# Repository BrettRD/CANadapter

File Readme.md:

# CANadapter

This is a basic CAN bus adapter based on the MCP2515 and the MCP2551.
The design is largely compatible with the Sparkfun CAN-BUS Shield for the sake of everyone's sanity.

The connectors are intended to be pin-compatible with Pmod, but there doesn't seen to be a standard or even defacto pinout for CANbus on Pmod online.

Board images generated by gerblook.org

##Major design goals:
* Full electrical isolation
* Hardy CAN front-end
* Support CAN bus development on the FPGA driven icoBoard.

## Parts List:
### CAN interface:
* 1x MCP2551 soic8 - CAN interface chip
* 1x PESD1CAN sot23 - TVS diode
* 2x TLP2361 fast optocoupler - optoisolation
* 2x 60R 1210 resistor - termination resistors
* 1x 4.7nF 1206 capacitor - Common mode filter
* 1x 1uF 1206 capacitor
* 1x 100R 0603 resistor
* 1x 330R 0603 resistor
* 1x 4K7 0603 resistor
* 1x 4pin header

### CAN Controller:
* 1x MCP2515 soic18 7.5mm - CAN controller IC
* 1x 16MHz 5032 crystal
* 1x 1uF 1206 capacitor
* 2x 18pF 0603 capacitor
* 1x 2x6pin header

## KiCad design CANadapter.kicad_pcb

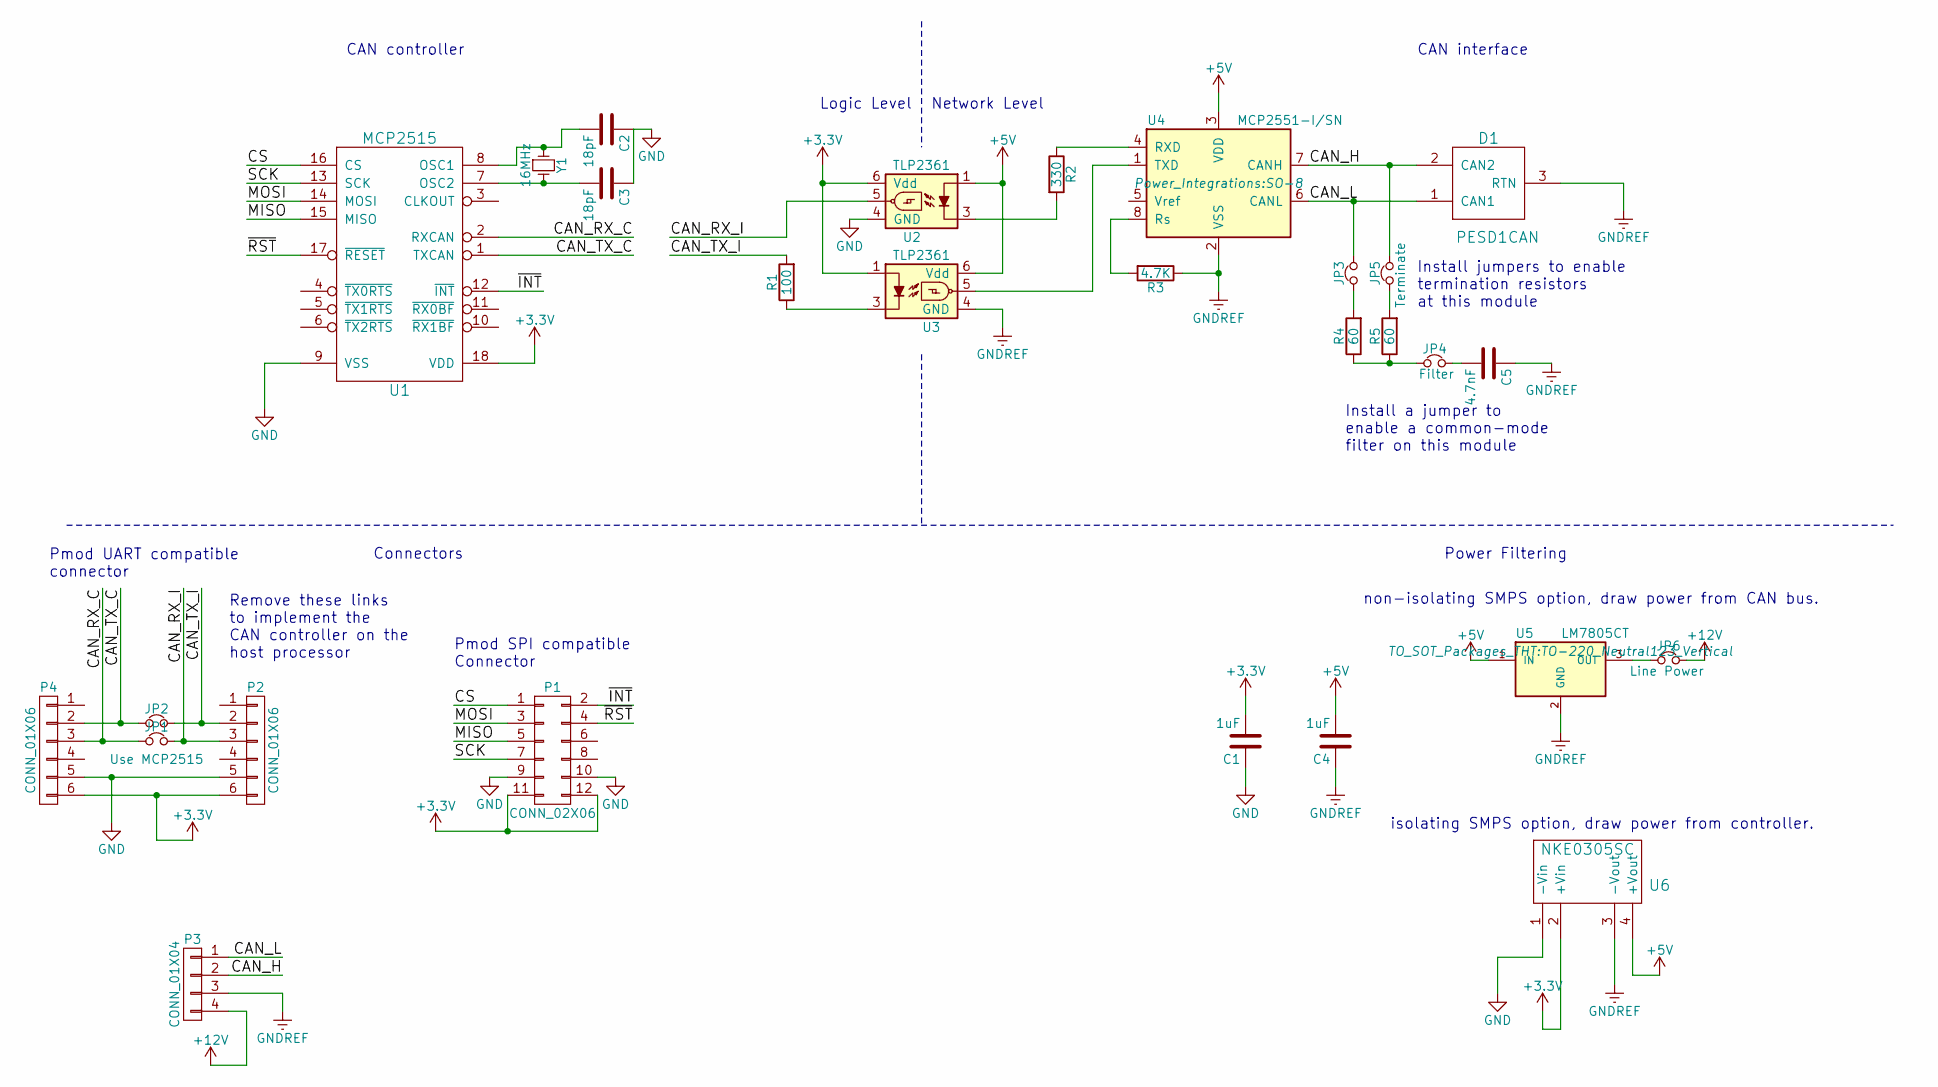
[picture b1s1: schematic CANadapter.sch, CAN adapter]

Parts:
C1, C4: 1uF; C_1210
C2, C3: 18pF; C_0603
C5: 4.7nF; C_1206
D1: PESD1CAN; SOT-23_Handsoldering
JP1, JP2: Use MCP2515; JumperSingleClosed
JP3, JP5: Terminate; JumperSingle
JP4: Filter; JumperSingle
JP6: Line Power; JumperSingle
P1: CONN_02X06; Pin_Header_Straight_2x06
P2, P4: CONN_01X06; Pin_Header_Straight_1x06
P3: CONN_01X04; Pin_Header_Straight_1x04
R1: 100; R_0603
R2: 330; R_0603
R3: 4.7K; R_0603
R4, R5: 60; R_1210
U1: MCP2515; SOIC-18_7.5x11.6mm_Pitch1.27mm
U2, U3: TLP2361; soic-5
U4: MCP2551-I/SN; SO-8
U5: LM7805CT; TO-220_Neutral123_Vertical
U6: NKE0305SC; Murata_SIL
Y1: 16MHz; Crystal_SMD_5032_2Pads

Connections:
+3V3: C1.2, P1.11, P1.12, P2.6, P4.6, U1.18 (VDD), U2.6 (Vdd), U3.1, U6.2 (+Vin)
+5V: C4.2, U2.1, U3.6 (Vdd), U4.3 (VDD), U5.1 (IN), U6.4 (+Vout)
+12V: JP6.1, P3.4
/CAN_H: D1.2 (CAN2), JP5.1, P3.2, U4.7 (CANH)
/CAN_L: D1.1 (CAN1), JP3.2, P3.1, U4.6 (CANL)
/CAN_RX_C: JP1.1, P4.3, U1.2 (RXCAN)
/CAN_RX_I: JP1.2, P2.3, U2.5
/CAN_TX_C: JP2.1, P4.2, U1.1 (TXCAN)
/CAN_TX_I: JP2.2, P2.2, R1.2
/CS: P1.1, U1.16 (CS)
/MISO: P1.5, U1.15 (MISO)
/MOSI: P1.3, U1.14 (MOSI)
/SCK: P1.7, U1.13 (SCK)
/~INT: P1.2, U1.12 (~INT)
/~RST: P1.4, U1.17 (~RESET)
GND: C1.1, C2.1, C3.1, P1.9, P1.10, P2.5, P4.5, U1.9 (VSS), U2.4 (GND), U6.1 (-Vin)
GNDREF: C4.1, C5.1, D1.3 (RTN), P3.3, R3.1, U3.4 (GND), U4.2 (VSS), U5.2 (GND), U6.3 (-Vout)
unnamed: C2.2, U1.8 (OSC1), Y1.1
unnamed: C3.2, U1.7 (OSC2), Y1.2
unnamed: C5.2, JP4.2
unnamed: JP3.1, R4.2
unnamed: JP4.1, R4.1, R5.1
unnamed: JP5.2, R5.2
unnamed: JP6.2, U5.3 (OUT)
unnamed: R1.1, U3.3
unnamed: R2.1, U4.4 (RXD)
unnamed: R2.2, U2.3
unnamed: R3.2, U4.8 (Rs)
unnamed: U3.5, U4.1 (TXD)

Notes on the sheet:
Pmod UART compatible connector
Logic Level
Network Level
Install jumpers to enable termination resistors at this module
Install a jumper to enable a common-mode filter on this module
Remove these links to implement the CAN controller on the host processor
non-isolating SMPS option, draw power from CAN bus.
Pmod SPI compatible Connector
CAN controller
CAN interface
Connectors
Power Filtering
isolating SMPS option, draw power from controller.

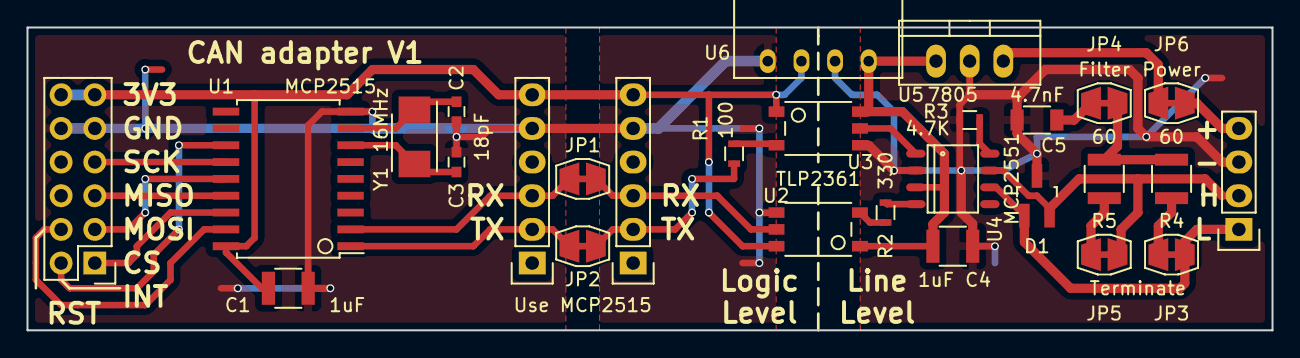
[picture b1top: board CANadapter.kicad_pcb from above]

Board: 2 copper layers, 94.0 x 22.9 mm, 28 parts (0 on the bottom side), 29 nets.

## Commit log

2016-02-02 Basic structure of schematic
2016-02-02 added schematic PDF
2016-02-03 Changed CAN termination, added resonator and jumpers
2016-02-03 Added basic voltage regulator on line side
2016-03-02 Changed CANtx/rx connector, tidied the schematic
2016-03-02 most footprints associated and roughly placed
2016-03-21 corrected connectivity and pin numbering, placed parts
2016-03-22 Partial layout
2016-05-21 substituted footprints, layout first pass complete
2016-05-29 added isolating smps, moved jumpers, added ground pours
2016-06-16 finished routing, improved silk
2016-06-16 improved silk
2016-06-16 ready for beta round
